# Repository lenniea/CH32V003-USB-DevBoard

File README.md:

# CH32V003-USB-DevBoard

## Description

This is a CH32V003 USB-capable dev board (Prototype Stage).

It features:
* USB-C connector
* Optional Crystal
* User Button at PD7 (also for Reset)
* User LED at PC0
* USB (bit-bang) on PD3/PD4

## Sponsors

[AISLER](https://aisler.net/) is the sponsor for the prototypes and the first batch of PCBs!

You can get PCBs manufactured in two business days starting at just 10.16€.
Use the code `alexander_m` to get 5€ off your next order!

## Purchase

If you want to have some assembled boards, you can purchase them on [Lectronz](https://www.lectronz.com/products/ch32v003-usb-development-board)!

## Images

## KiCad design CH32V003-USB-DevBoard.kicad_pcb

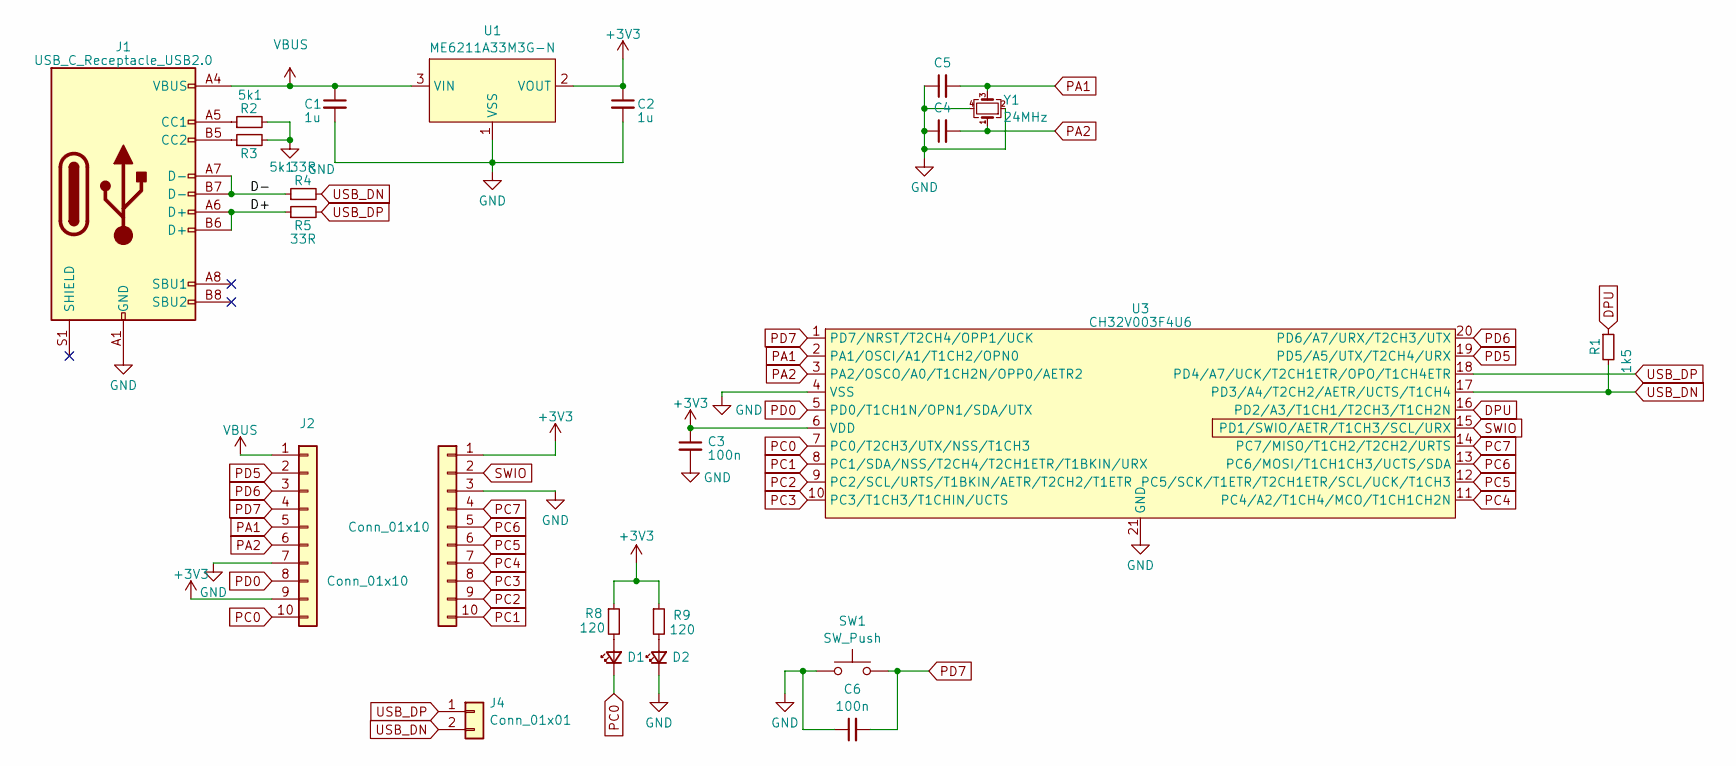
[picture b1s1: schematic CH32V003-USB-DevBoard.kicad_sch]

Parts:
C1, C2: 1u; C_0402_1005Metric; LCSC C52923
C3, C6: 100n; C_0402_1005Metric; LCSC C1525
C4, C5: 20p; C_0402_1005Metric; LCSC C882541
D1, D2: LED_Small; LED_0402_1005Metric; LCSC C5160702
J1: USB_C_Receptacle_USB2.0; USB_C_Receptacle_HRO_TYPE-C-31-M-12; LCSC C2927039
J2, J3: Conn_01x10; PinHeader_1x10_Small
J4: Conn_01x01; TestPoint_01x02
R1: 1k5; R_0402_1005Metric; LCSC C25867
R2, R3: 5k1; R_0402_1005Metric; LCSC C25905
R4, R5: 33R; R_0402_1005Metric; LCSC C25867
R8, R9: 120; R_0402_1005Metric; LCSC C25867
SW1: SW_Push; SW_SPST_B3U-1000P-B; LCSC C231329
U1: ME6211A33M3G-N; SOT-23-3; LCSC C168807
U3: CH32V003F4U6; ETSSOP-20-1EP_4.4x6.5mm_P0.65mm_EP3x4.2mm; LCSC C5299908
Y1: 24MHz; Crystal_SMD_2016-4Pin_2.0x1.6mm; LCSC C2875241

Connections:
+3V3: C2.1, C3.1, J2.9, J3.1, R8.1, R9.1, U1.2 (VOUT), U3.6 (VDD)
/D+: J1.A6 (D+), J1.B6 (D+), R5.1
/D-: J1.A7 (D-), J1.B7 (D-), R4.1
DPU: R1.1, U3.16 (PD2/A3/T1CH1/T2CH3/T1CH2N)
GND: C1.2, C2.2, C3.2, C4.1, C5.1, C6.1, D2.1 (K), J1.A1 (GND), J1.A12 (GND), J1.B1 (GND), J1.B12 (GND), J2.7, J3.3, R2.2, R3.2, SW1.1, U1.1 (VSS), U3.4 (VSS), U3.21 (GND), Y1.2, Y1.4
unnamed: D1.2 (A), R8.2
unnamed: D2.2 (A), R9.2
unnamed: J1.A5 (CC1), R2.1
unnamed: J1.B5 (CC2), R3.1
PA1: C5.2, J2.5, U3.2 (PA1/OSCI/A1/T1CH2/OPN0), Y1.3
PA2: C4.2, J2.6, U3.3 (PA2/OSCO/A0/T1CH2N/OPP0/AETR2), Y1.1
PC0: D1.1 (K), J2.10, U3.7 (PC0/T2CH3/UTX/NSS/T1CH3)
PC1: J3.10, U3.8 (PC1/SDA/NSS/T2CH4/T2CH1ETR/T1BKIN/URX)
PC2: J3.9, U3.9 (PC2/SCL/URTS/T1BKIN/AETR/T2CH2/T1ETR)
PC3: J3.8, U3.10 (PC3/T1CH3/T1CHIN/UCTS)
PC4: J3.7, U3.11 (PC4/A2/T1CH4/MCO/T1CH1CH2N)
PC5: J3.6, U3.12 (PC5/SCK/T1ETR/T2CH1ETR/SCL/UCK/T1CH3)
PC6: J3.5, U3.13 (PC6/MOSI/T1CH1CH3/UCTS/SDA)
PC7: J3.4, U3.14 (PC7/MISO/T1CH2/T2CH2/URTS)
PD0: J2.8, U3.5 (PD0/T1CH1N/OPN1/SDA/UTX)
PD5: J2.2, U3.19 (PD5/A5/UTX/T2CH4/URX)
PD6: J2.3, U3.20 (PD6/A7/URX/T2CH3/UTX)
PD7: C6.2, J2.4, SW1.2, U3.1 (PD7/NRST/T2CH4/OPP1/UCK)
SWIO: J3.2, U3.15 (PD1/SWIO/AETR/T1CH3/SCL/URX)
USB_DN: J4.2, R1.2, R4.2, U3.17 (PD3/A4/T2CH2/AETR/UCTS/T1CH4)
USB_DP: J4.1, R5.2, U3.18 (PD4/A7/UCK/T2CH1ETR/OPO/T1CH4ETR)
VBUS: C1.1, J1.A4 (VBUS), J1.A9 (VBUS), J1.B4 (VBUS), J1.B9 (VBUS), J2.1, U1.3 (VIN)

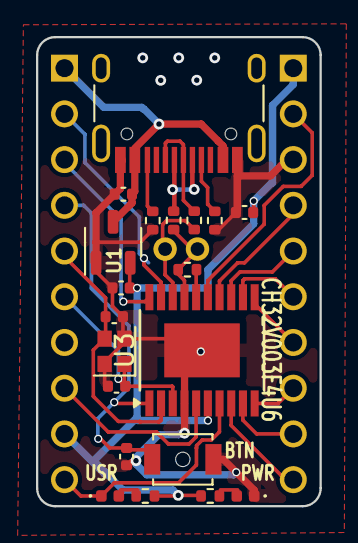
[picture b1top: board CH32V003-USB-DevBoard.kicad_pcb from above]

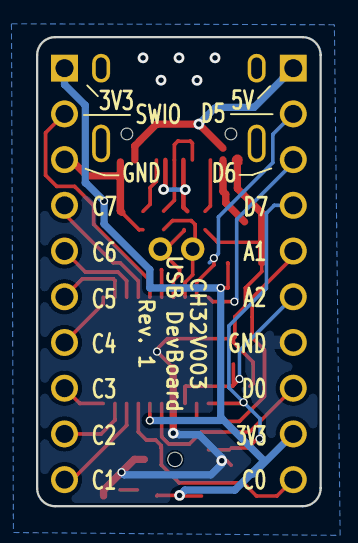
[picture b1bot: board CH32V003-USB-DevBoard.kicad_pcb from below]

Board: 2 copper layers, 15.8 x 26.1 mm, 23 parts (2 on the bottom side), 27 nets.
